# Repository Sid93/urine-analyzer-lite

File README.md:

# Urine Analyzer Lite

> Compact, automated urine dipstick reader by **Levram Lifesciences**.  
> Single-strip, N20-motor-driven, ESP32-S3 based with thermal print output.

---

## Overview

The Urine Analyzer Lite reads standard 10-pad reagent dipsticks using dual TCS34725 RGB color sensors and classifies results for 10 analytes. A compact N20 gear motor steps the strip under the optical head at controlled speed. Results print via an integrated CSN-A2 thermal printer.

**Key specs:**

| Parameter | Value |
|---|---|
| MCU | ESP32-S3-DevKitC-1 (Xtensa dual-core 240 MHz, 8 MB flash) |
| Sensors | TCS34725 ×2, SHT31, BH1750, ADS1115, HX711 |
| Display | 3.5" SPI TFT (ILI9488) + XPT2046 touch — see `hardware/ENGINEERING_REVIEW.md` |
| Motor | GA12-N20 6V 200RPM with Hall encoder + MX1508 H-bridge |
| Printer | CSN-A2 58mm thermal (ESC/POS) |
| Power | 3.7V 2000mAh LiPo → TP4056 USB-C charger → S13V25F5 5V regulator |
| Sterilization | 275nm UV-C LED (10s cycle post-scan) |
| Analytes | Leukocytes, Nitrites, Urobilinogen, Protein, pH, Blood, Specific Gravity, Ketones, Bilirubin, Glucose |
| Estimated BOM | ~$387 per unit (prototype); target <$250 at 50-unit volume |

---

## Repository Structure

```
urine-analyzer-lite/
├── hardware/
│   ├── schematic/
│   │   ├── gen_schematic.py          # KiCad schematic generator
│   │   └── urine_analyzer_lite.kicad_sch
│   └── cad/
│       └── main_chassis.scad         # OpenSCAD enclosure (all 3D-printed parts)
├── firmware/
│   └── main/
│       ├── main.ino                  # Arduino sketch (state machine)
│       ├── config.h                  # Pin map and tunable constants
│       ├── sensors.h                 # All sensor drivers
│       ├── motor.h                   # N20 motion control + homing
│       ├── analysis.h                # HSV pad classification (10 analytes)
│       └── printer.h                 # ESC/POS thermal print
├── bom/
│   └── bom.csv                       # Full bill of materials (~40 items)
├── TODO.md                           # Project checklist
└── README.md
```

---

## Hardware

### Schematic
Open in KiCad 7+:
```
File → Open → hardware/schematic/urine_analyzer_lite.kicad_sch
```
To regenerate after edits:
```bash
cd hardware/schematic && python3 gen_schematic.py
```

### CAD
Open in OpenSCAD ≥ 2021.01:
```
hardware/cad/main_chassis.scad
```
All 3D-printable parts are exported from one file. Render individual modules:
```
openscad -o chassis_base.stl main_chassis.scad
```

**Print settings:**

| Part | Material | Infill | Layer |
|---|---|---|---|
| Chassis base, MCU tray, dipstick tray | PLA | 20% | 0.2 mm |
| Optical chamber, UV-C shield | Black PLA | 100% | 0.1 mm |
| Sensor mounts, printer bracket, belt parts | PETG | 30% | 0.2 mm |

---

## Firmware

### Requirements
- Arduino IDE ≥ 2.3 with ESP32 board package ≥ 2.0.14
- Board: **ESP32S3 Dev Module** — Flash: 8MB, PSRAM: OPI, USB: Hardware CDC

### Libraries (Arduino Library Manager)
```
Adafruit TCS34725      >= 1.4.2
Adafruit ADS1X15       >= 2.5.0
Adafruit SHT31         >= 2.2.2
BH1750 by Christopher Laws >= 1.3.0
HX711 by bogde         >= 0.7.5
```

### Flash
1. Open `firmware/main/main.ino` in Arduino IDE  
2. Select board and port  
3. Upload

### Calibration (required before first use)
1. **White standard** — place Spectralon pad under optical head; record R/G/B values in `config.h` (`CAL_R/G/B_WHITE`)
2. **Scale** — place known weight on scale platform; adjust `scale.set_scale()` factor in `sensors.h`
3. **Motor steps** — measure real pad pitch with calipers; adjust `TICKS_PER_PAD` in `config.h`
4. **Hue ranges** — run known positive/negative strips; refine `PAD_TABLE[]` in `analysis.h`

---

## Operation

1. Insert dipstick tray with strip face-up
2. Place sample cup on weight sensor (minimum 1 g detected)
3. Press scan button
4. Device homes, steps across all 10 pads, classifies, prints report
5. UV-C sterilization cycle runs automatically (10 s)
6. Remove strip; device returns to IDLE

---

## Bill of Materials

See [`bom/bom.csv`](bom/bom.csv) — estimated prototype total: **$387 USD**.

---

## License

Hardware and firmware © Levram Lifesciences. All rights reserved.  
*For clinical use by qualified personnel only.*

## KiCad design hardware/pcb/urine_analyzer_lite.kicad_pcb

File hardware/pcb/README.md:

# PCB — Urine Analyzer Lite (Design A)

A **starting board** generated from the netlist model via KiCad's `pcbnew` Python API.
All 31 footprints are placed and net-assigned; the board is **not yet routed**.

## Files
- `build_pcb.py` — generator (run with KiCad's bundled Python; needs `pcbnew`).
- `urine_analyzer_lite.kicad_pcb` — the board (31 footprints, real footprints, nets assigned).
- `urine_analyzer_lite.kicad_pro` — project file (open this in KiCad).
- `urine_analyzer_lite_render_top.png` — 3D render (top).
- `DRC_report.txt` / `drc.json` — DRC output.

## Validation (KiCad 10.0.3)
- **Schematic parity: 0 mismatches** — the board's connectivity matches the schematic exactly.
- **104 unconnected items** — this is the **unrouted ratsnest** (expected; the engineer routes it).
- **214 DRC violations** — all are **placement-density cosmetics** from the auto-grid layout:
  `silk_over_copper`/`silk_overlap` (ref-text overlap), `courtyards_overlap`,
  `pth_inside_courtyard`, a few `clearance`/`solder_mask_bridge`. They disappear once parts are
  spread out and routed. **None are structural / netlist errors.**

## What the engineer does
1. Open the project in KiCad 10. **Confirm footprints** — modules are generic 2.54mm pin
   headers; verify each header's **pin ORDER against the module datasheet/silkscreen**
   (the auto-assignment uses the netlist order, see `footprints.py` + `../netlist/NETLIST.md`).
2. Re-place parts sensibly (optical chamber sensors together, printer/motor power near the
   regulator, keep UV-C/printer high-current away from sensor analog lines).
3. Add **power planes** (GND / +5V / +3V3), route — wide traces for motor/printer/UV-C per
   `../POWER_BUDGET.md`. Add mounting holes to the chassis stand-offs.
4. **DRC → 0**, then export Gerbers + drill + position:
   ```
   kicad-cli pcb export gerbers -o gerbers/ urine_analyzer_lite.kicad_pcb
   kicad-cli pcb export drill   -o gerbers/ urine_analyzer_lite.kicad_pcb
   ```

## Regenerate
```bash
/Applications/KiCad.app/Contents/Frameworks/Python.framework/Versions/3.9/bin/python3 build_pcb.py
```

> Starting board for engineer verification, not a finished layout. Placement, routing, footprint
> confirmation (esp. module pin order), stackup, and DRC sign-off are the engineer's.

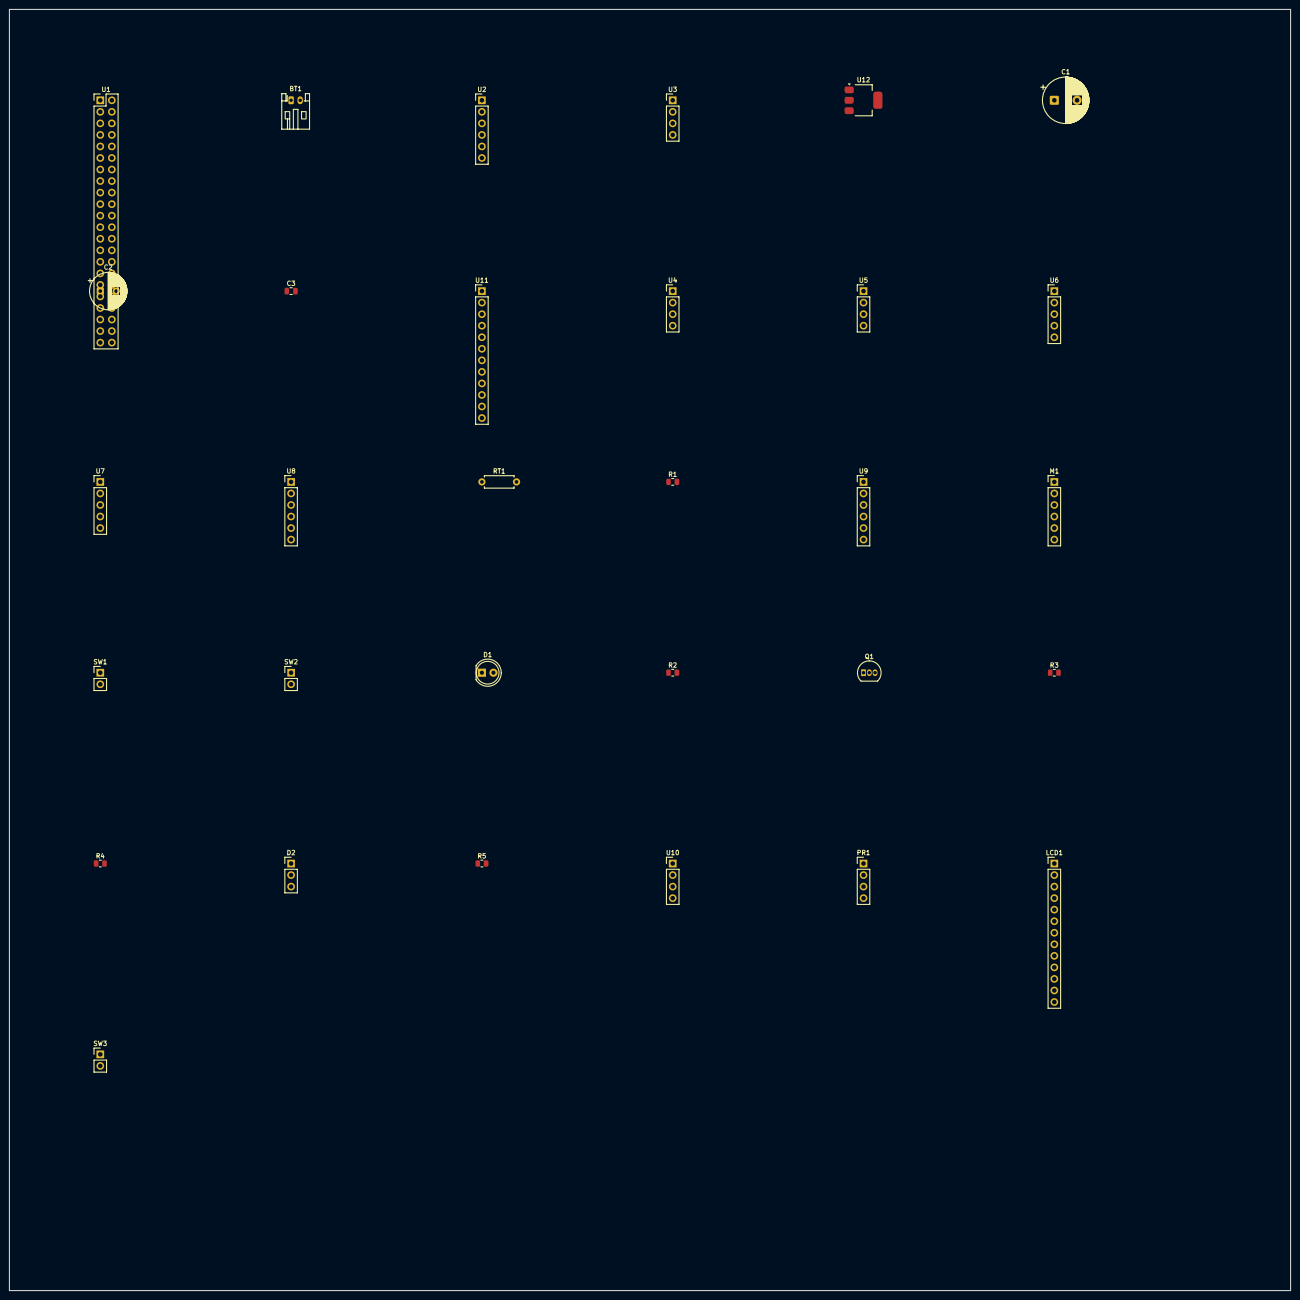
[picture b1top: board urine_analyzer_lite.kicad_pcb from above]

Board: 2 copper layers, 282.0 x 282.0 mm, 31 parts (0 on the bottom side), 38 nets, no tracks yet.

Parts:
BT1: LiPo 3.7V 2000mAh; JST_PH_S2B-PH-K_1x02_P2.00mm_Horizontal
C1: 1000uF/10V; CP_Radial_D10.0mm_P5.00mm
C2: 470uF/10V; CP_Radial_D8.0mm_P3.50mm
C3: 10uF/10V; C_0805_2012Metric
D1: High-CRI 95+ LED; LED_D5.0mm_Clear
D2: 275nm UVC module; PinHeader_1x03_P2.54mm_Vertical
LCD1: 3.5in SPI TFT ILI9488 +touch; PinHeader_1x13_P2.54mm_Vertical
M1: GA12-N20 6V 200RPM +enc; PinHeader_1x06_P2.54mm_Vertical
PR1: CSN-A2 thermal; PinHeader_1x04_P2.54mm_Vertical
Q1: 2N7000; TO-92_Inline
R1: 10k; R_0805_2012Metric
R2: 100R; R_0805_2012Metric
R3: 220R; R_0805_2012Metric
R4, R5: 100k; R_0805_2012Metric
RT1: NTC 10k B3950; R_Axial_DIN0207_L6.3mm_D2.5mm_P7.62mm_Horizontal
SW1, SW2: KW12-3; PinHeader_1x02_P2.54mm_Vertical
SW3: Tactile 6x6; PinHeader_1x02_P2.54mm_Vertical
U1: ESP32-S3-DevKitC-1; PinHeader_2x22_P2.54mm_Vertical
U2: TP4056 USB-C; PinHeader_1x06_P2.54mm_Vertical
U3: S13V25F5 buck-boost; PinHeader_1x04_P2.54mm_Vertical
U4, U5: TCS34725; PinHeader_1x04_P2.54mm_Vertical
U6: SHT31-D; PinHeader_1x05_P2.54mm_Vertical
U7: BH1750; PinHeader_1x05_P2.54mm_Vertical
U8: ADS1115; PinHeader_1x06_P2.54mm_Vertical
U9: MX1508; PinHeader_1x06_P2.54mm_Vertical
U10: HX711 1kg kit; PinHeader_1x04_P2.54mm_Vertical
U11: TCA9548A; PinHeader_1x12_P2.54mm_Vertical
U12: AMS1117-3.3; SOT-223-3_TabPin2

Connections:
+3V3: C3.1, M1.3, RT1.1, U4.1, U5.1, U6.1, U7.1, U8.1, U10.1, U11.1, U11.5, U12.2
+5V: C1.1, C2.1, D1.2, D2.1, LCD1.1, PR1.1, U1.1, U3.3, U3.4, U9.1, U12.3
ENC_A: M1.5, U1.8
ENC_B: M1.6, U1.9
GND: BT1.2, C1.2, C2.2, C3.2, D2.2, LCD1.2, M1.4, PR1.2, Q1.1, R1.2, R4.2, R5.2, SW1.1, SW2.1, SW3.2, U1.2, U1.3, U2.2, U2.4, U2.6, U3.2, U4.2, U5.2, U6.2, U6.5, U7.2, U7.5, U8.2, U8.5, U9.2, U10.2, U11.2, U11.6, U11.7, U11.8, U12.1
HX_DT: U1.14, U10.3
HX_SCK: U1.15, U10.4
I2C_SCL: U1.5, U6.4, U7.4, U8.4, U11.4
I2C_SDA: U1.4, U6.3, U7.3, U8.3, U11.3
LED_DRAIN: Q1.3, R2.2
LED_GATE: Q1.2, R3.2, R4.1
LED_NODE: D1.1, R2.1
LED_PWM: R3.1, U1.12
LIM_END: SW2.2, U1.11
LIM_HOME: SW1.2, U1.10
MOTOR_A: M1.1, U9.5
MOTOR_B: M1.2, U9.6
MOT_IN1: U1.6, U9.3
MOT_IN2: U1.7, U9.4
NTC_SENSE: R1.1, RT1.2, U8.6
PRN_RX: PR1.4, U1.18
PRN_TX: PR1.3, U1.17
SCAN_BTN: SW3.1, U1.16
TCS1_SCL: U4.4, U11.10
TCS1_SDA: U4.3, U11.9
TCS2_SCL: U5.4, U11.12
TCS2_SDA: U5.3, U11.11
TFT_BL: LCD1.8, U1.25
TFT_CS: LCD1.3, U1.23
TFT_DC: LCD1.5, U1.24
TFT_MISO: LCD1.9, LCD1.13, U1.22
TFT_MOSI: LCD1.6, LCD1.12, U1.21
TFT_RST: LCD1.4, U1.19
TFT_SCLK: LCD1.7, LCD1.10, U1.20
TOUCH_CS: LCD1.11, U1.26
UVC_EN: D2.3, R5.1, U1.13
VBAT: BT1.1, U2.3
VSYS: U2.5, U3.1

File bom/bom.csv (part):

Ref,Name,Description,Category,Type,Qty,Unit Cost (INR),Total Cost (INR),India Supplier,India URL,Sourcing Note
U1,ESP32-S3-DevKitC-1,Dual-core MCU with native USB; 8MB flash + 8MB OPI PSRAM,Electrical,MCU,1,1299,1299,Robocraze,https://robocraze.com/products/esp32-s3-devkitc-1-n8r8,Also on Amazon.in ~₹1350; Evelta stocks too
U2,TP4056 USB-C Module,LiPo charging module with USB-C input and protection circuit,Electrical,Power,1,65,65,Robocraze,https://robocraze.com/products/tp4056-type-c-usb-5v-1a-18650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,Very common; also at Probots / Amazon.in ~₹60
U3,S13V25F5 Buck-Boost Regulator,5 V 2.5 A step-up/step-down regulator from LiPo,Electrical,Power,1,1099,1099,Mouser India,https://www.mouser.in/ProductDetail/Pololu/2775,Pololu product; Mouser.in stocks it. element14.in alternate
BT1,3.7V 2000mAh LiPo,Main rechargeable power source,Electrical,Power,1,599,599,Robocraze,https://robocraze.com/products/3-7v-2000mah-lipo-battery,Probots also carries; verify protection circuit included
U4,TCS34725 RGB Sensor #1,I2C RGB+clear color sensor with IR cut filter (primary pad sensor),Electrical,Sensor,1,649,649,Robocraze,https://robocraze.com/products/tcs34725-rgb-color-sensor-module,Evelta ~₹700; confirm IR-cut filter present on module
U5,TCS34725 RGB Sensor #2,I2C RGB+clear color sensor (secondary / differential),Electrical,Sensor,1,649,649,Robocraze,https://robocraze.com/products/tcs34725-rgb-color-sensor-module,Same part as U4; buy 2 together for small discount
U6,SHT31-D Module,High-accuracy I2C temperature and humidity sensor,Electrical,Sensor,1,749,749,Probots,https://probots.co.in/sht31-d-temperature-humidity-sensor-br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,Robocraze alternate ~₹780; avoid clone modules for accuracy
U7,BH1750 FVI,I2C digital ambient light sensor,Electrical,Sensor,1,149,149,Robocraze,https://robocraze.com/products/bh1750-light-intensity-sensor-module,Amazon.in ~₹160; very common; GY-302 breakout widely available
U8,ADS1115 ADC Module,16-bit I2C ADC with PGA for NTC thermistor,Electrical,Module,1,449,449,Robocraze,https://robocraze.com/products/ads1115-16-bit-adc-4-channel-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,Probots ~₹400; Evelta ~₹480
RT1,NTC Thermistor 10k B3950,Temperature sensing inside optical chamber,Electrical,Sensor,1,25,25,Electronicscomp,https://www.electronicscomp.com/10k-ohm-ntc-thermistor-india,Sunrom.com ~₹20; sold in packs of 5 — buy pack
U9,MX1508 Dual H-Bridge,Dual DC motor driver 2A per channel,Electrical,Module,1,120,120,Robocraze,https://robocraze.com/products/mx1508-dual-dc-motor-driver-module,Amazon.in ~₹100; Robokits ~₹110
M1,GA12-N20 6V 200RPM + Encoder,Compact DC gear motor with Hall-effect quadrature encoder,Electrical,Actuator,1,449,449,Robocraze,https://robocraze.com/products/n20-dc-gear-motor-with-encode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,Robokits ~₹500; confirm 6V 200RPM variant with encoder
SW1,KW12-3 Micro Limit Switch,Home position limit switch (NO),Electrical,Sensor,1,65,65,Robocraze,https://robocraze.com/products/micro-limit-switch,Amazon.in ₹50–80; buy pack of 5 for spares
SW2,KW12-3 Micro Limit Switch,End-of-travel limit switch (NO),Electrical,Sensor,1,65,65,Robocraze,https://robocraze.com/products/micro-limit-switch,Same as SW1; order 4 total (2 working + 2 spares)
D1,High-CRI 5mm LED 95+ CRI,High colour-rendering white illumination LED for pad reading,Electrical,Actuator,1,220,220,Mouser India,https://www.mouser.in/c/?q=95+CRI+5mm+LED,IMPORT — no Indian-stocked 95+CRI 5mm LED equivalent; Nichia NSPWR70CSS-K1 via Mouser.in. Budget alternative: 90CRI Cree-equiv from Amazon.in ~₹80
Q1,2N7000 N-Channel MOSFET,PWM control MOSFET for illumination LED,Electrical,Module,1,15,15,Electronicscomp,https://www.electronicscomp.com/2n7000-n-channel-mosfet-tran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,Sunrom.com ~₹20; sold loose — buy 10 for <₹100
D2,275nm UVC LED Module,UV-C sterilization LED for tray decontamination,Electrical,Actuator,1,1050,1050,Mouser India,https://www.mouser.in/c/?q=UVC+LED+275nm,IMPORT — Mouser.in stocks Klaran / SETi UVC LEDs; order with heatsink. element14.in alternate. Allow 2-week lead time
U10,HX711 Load Cell Amplifier Kit 1kg,24-bit ADC for load cell weight measurement,Electrical,Module,1,320,320,Robocraze,https://robocraze.com/products/hx711-weight-sensor-load-cell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,Includes 1 kg bar-type load cell; Probots ~₹350
PR1,CSN-A2 Micro Thermal Printer,58mm thermal receipt printer for diagnostic reports,Electrical,Actuator,1,2800,2800,Robocraze,https://robocraze.com/products/mini-thermal-receipt-printer-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,Amazon.in ₹2500–3200 depending on seller; verify TTL UART version (not USB-only)
LCD1,3.5in SPI TFT (ILI9488) with XPT2046 touch,SPI display 480x320 with resistive touch; ESP32-S3 native SPI,Electrical,Display,1,950,950,Robocraze,https://robocraze.com/products/3-5-inch-tft-lcd-touch-screen,REPLACES Waveshare 4.3in DSI LCD — ESP32-S3 has no MIPI-DSI. ST7796 4.0in is a drop-in alt. Amazon.in ₹850–1200
U11,TCA9548A I2C Multiplexer,8-channel I2C mux to separate the two TCS34725 (both fixed at 0x29),Electrical,Module,1,299,299,Robocraze,https://robocraze.com/products/tca9548a-i2c-multiplexer,REQUIRED — two TCS34725 cannot share 0x29 on one bus. Evelta/Probots alternates ~₹320
U12,AMS1117-3.3 Regulator,3.3V LDO from 5V rail for the sensor bus (no dedicated 3V3 rail otherwise),Electrical,Power,1,35,35,Electronicscomp,https://www.electronicscomp.com/ams1117-3.3v-voltage-regulator,Sold on small breakout ~₹40; or use ESP32-S3 DevKit 3V3 pin if sensor current stays low (verify budget)
SW3,Momentary Tactile Button 6x6mm,Scan trigger button,Electrical,Sensor,1,5,5,Electronicscomp,https://www.electronicscomp.com/6x6mm-push-button-tactile-sw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,Sunrom ~₹4; buy strip of 20 (<₹80 total)
--,GT2 Timing Belt 200mm 6mm wide,Belt drive for strip-tray linear motion,Mechanical,Mechanism,1,199,199,Robocraze,https://robocraze.com/products/gt2-timing-belt-6mm-width-200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,Amazon.in ~₹180; buy 2 (one spare)
--,GT2 Pulley 16T 3mm bore,Aluminium motor and idler pulleys,Mechanical,Mechanism,2,175,350,Robocraze,https://robocraze.com/products/gt2-timing-pulley-16-teeth-3mm-bore,Amazon.in ~₹150 each
--,M3 Stainless Socket Head Screws M3×10,General chassis fasteners,Mechanical,Hardware,20,4,80,Amazon India,https://www.amazon.in/s?k=M3+stainless+socket+head+screw+10mm,Buy 50-pack ~₹150 for spares
--,M3 Brass Heat-Set Inserts M3×5,Threaded inserts for 3D-printed parts,Mechanical,Hardware,12,8,96,Amazon India,https://www.amazon.in/s?k=M3+brass+heat+set+insert,Robocraze carries too; buy 20-pack
--,Frosted Acrylic Sheet 50×20×2mm,LED diffuser plate in optical chamber,Mechanical,Structural,1,180,180,Amazon India,https://www.amazon.in/s?k=frosted+acrylic+sheet+2mm,Cut from A4 sheet ~₹300; local acrylic shop in most cities cheaper
--,2mm Clear Acrylic Sheet (laser cut),Strip flattening guard over tray,Mechanical,Structural,1,250,250,Amazon India,https://www.amazon.in/s?k=clear+acrylic+sheet+2mm,Local laser cutting shop (Lamington Rd Mumbai / Nehru Place Delhi) cheaper than online
--,Aluminium Sheet 80×40×2mm,UV-C safety shield (internal),Mechanical,Structural,1,320,320,Amazon India,https://www.amazon.in/s?k=aluminium+sheet+2mm,Local hardware/metal supplier; cut from 200×200mm sheet
--,Spectralon 99% White Standard 10×10mm,White calibration standard for sensor normalisation,Mechanical,Calibration,1,2200,2200,Labsphere (import),https://www.labsphere.com/product/spectralon-diffuse-reflect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,IMPORT — no India distributor; ship via FedEx International. DIY alternative: pressed BaSO4 tablet (~₹200 at lab chemicals supplier like HiMedia)
--,Whatman Grade 1 Filter Paper Strips,Disposable tray liners pack of 100,Mechanical,Consumable,100,12,1200,Merck India,https://www.merckmillipore.com/IN/en/product/Whatman-Grade-1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,HiMedia Laboratories (Mumbai/Delhi/Chennai) alternate; also Amazon.in ~₹1400 for pack
--,Chassis Base (3D print – PLA),Compact main chassis 160×120×55mm,Mechanical,3D Printed,1,300,300,Self / Local bureau,N/A,PLA ~₹900/kg on Amazon.in (eSun / Bambu); 3D printing bureaus in major cities ~₹5–8/gram
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
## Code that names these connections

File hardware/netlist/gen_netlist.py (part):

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        "5V":   ("5V",     "+5V"),
        "GND1": ("GND",    "GND"),
        "GND2": ("GND",    "GND"),
        "1":    ("GPIO1",  "I2C_SDA"),
        "2":    ("GPIO2",  "I2C_SCL"),
        "4":    ("GPIO4",  "MOT_IN1"),
        "5":    ("GPIO5",  "MOT_IN2"),
        "6":    ("GPIO6",  "ENC_A"),
        "7":    ("GPIO7",  "ENC_B"),
        "10":   ("GPIO10", "LIM_HOME"),
        "11":   ("GPIO11", "LIM_END"),
        "12":   ("GPIO12", "LED_PWM"),
        "13":   ("GPIO13", "UVC_EN"),
        "14":   ("GPIO14", "HX_DT"),
        "15":   ("GPIO15", "HX_SCK"),
        "16":   ("GPIO16", "SCAN_BTN"),
        "17":   ("GPIO17", "PRN_TX"),
        "18":   ("GPIO18", "PRN_RX"),
        "21":   ("GPIO21", "TFT_RST"),
        "38":   ("GPIO38", "TFT_SCLK"),
        "39":   ("GPIO39", "TFT_MOSI"),
        "40":   ("GPIO40", "TFT_MISO"),
        "41":   ("GPIO41", "TFT_CS"),
        "42":   ("GPIO42", "TFT_DC"),
        "47":   ("GPIO47", "TFT_BL"),
        "48":   ("GPIO48", "TOUCH_CS"),
     }),

    # ── Power path ──
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
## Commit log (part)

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2026-06-04 Add PCB Roadmap & Datasheet to Dr. Praveen
    Schematic Task.
    1. Connect the ESP 32 microcontroller with colour sensor
    2. Connect the microcontroller with 2.4 inch touch display
    3. Connect the microcontroller with thermal printer via driver
    4. Connect with USB connector and programmer to programme microcontroller
    5. Connection of power supply like 230 with 9V, 5V, 3.3 V etc..
2026-06-04 Add files via upload
    Datasheets...!!
2026-06-04 Add files via upload
    Microcontroller Datasheet
